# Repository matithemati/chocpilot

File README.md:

# ChocPilot

ChocPilot to przewodowy macropad z **8 niskoprofilowymi klawiszami Kailh Choc** (matryca 2×4)
i **ekranem OLED 2,42" (SSD1309, 128×64)** na **Arduino Pro Micro** (ATmega32U4), oraz aplikacja
na Windows, w której ustawiasz, co robi każdy klawisz.

Firmware jest „cienki”: skanuje klawisze, rysuje ekran i przechowuje kilka ustawień. Całą logikę
(gesty, akcje, profile) wykonuje aplikacja na PC. Komunikują się przez USB CDC protokołem
JSON Lines ([docs/PROTOCOL.md](docs/PROTOCOL.md)). Gdy aplikacja nie działa, urządzenie samo
wysyła zapisane skróty przez USB HID (tryb awaryjny).

Projekt powstał z kodu macropada Tap32 (3×3 MX + enkoder) – ChocPilot nie ma pokrętła.

```
firmware/   PlatformIO: środowiska promicro (5 V), promicro_3v3, native (testy)
app/        aplikacja Python 3.12+ (PySide6): rdzeń, GUI, symulator, testy
docs/       PROTOCOL.md, WIRING.md, schematic.png (schemat płytki)
```

## Funkcje

- **Gesty**: naciśnięcie, przytrzymanie (próg 500 ms), podwójne naciśnięcie (okno 300 ms).
- **Akcje**: uruchom program (albo przełącz na jego okno; przy kilku oknach kolejne naciśnięcia
  przechodzą między nimi), otwórz plik/folder, adres WWW,
  skrót klawiszowy (także Win, F13–F24), wpisz tekst (Unicode), multimedia, głośność
  systemu i pojedynczego programu, przewijanie, polecenie cmd/PowerShell, makro, zmiana
  profilu, warstwa (profil na czas trzymania klawisza), blokada komputera, wyłączenie ekranu.
- **Profile** z automatycznym przełączaniem według aktywnego okna (np. `obs64.exe` → „Stream”),
  import/eksport do JSON.
- **Ekran 128×64**: siatka etykiet 2×4 (jak klawisze) albo duża nazwa profilu, pasek głośności,
  etykieta po akcji, wygaszacz, znacznik online/offline, tryb testu sprzętu.
- **Tryb awaryjny HID**: po 3 s bez sygnału z aplikacji klawisze wysyłają skróty wyliczone
  z profilu (akcje „skrót” i „multimedia”); domyślnie dolny rząd: ciszej, głośniej,
  odtwarzaj/pauza, wycisz.

## Części

- 1× Arduino / SparkFun **Pro Micro** (ATmega32U4), 5 V/16 MHz albo 3,3 V/8 MHz
- 8× przełącznik **Kailh Choc** (low profile) + nasadki Choc, 8× dioda 1N4148
- 1× OLED **2,42" SSD1309 128×64 I²C** – moduł ShengYang, wersja **4-pinowa I²C**
  (70,10 × 48,10 mm, używana w projekcie); wersja 7-pinowa (72 × 43 mm) też pasuje do obudowy
  (`oled_variant`), ale wymaga przełożenia rezystorów z SPI na I²C.
  Szczegóły i karta sprzedawcy: [docs/WIRING.md](docs/WIRING.md#oled-242-ssd1309-12864-ic-złącze-j1)
- płytka ChocPilot (schemat: [docs/schematic.png](docs/schematic.png))

## Montaż

Pełny opis i tabela pinów: **[docs/WIRING.md](docs/WIRING.md)**. Najważniejsze:

1. Matryca **COL2ROW** 2×4: przy każdym przełączniku dioda 1N4148, **pasek (katoda) w stronę
   wiersza**. S1–S4 = klawisze K1–K4 (Row 0), S5–S8 = K5–K8 (Row 1).
2. OLED na złączu J1: GND, **+5 V**, SDA (pin 2 Pro Micro), SCL (pin 3). Sprawdź kolejność
   wyprowadzeń modułu – jeśli SDA i SCL są zamienione, firmware sam to wykryje (programowe I²C).
3. Uruchom tryb testu sprzętu (przytrzymaj **K1 + K4** zaraz po podłączeniu, przez 3 s) i sprawdź
   każdy klawisz.

## Firmware

Wymagania: [PlatformIO](https://platformio.org/) (VS Code + rozszerzenie albo `pip install platformio`).

```bash
cd firmware
pio run -e promicro
```

(`promicro` – Pro Micro 5 V/16 MHz, `promicro_3v3` – wersja 3,3 V/8 MHz.)

Platforma `atmelavr`, płytka `sparkfun_promicro16` (albo `sparkfun_promicro8`), rdzeń Arduino AVR:
USB CDC + HID (PluggableUSB, klawiatura i consumer control). Nazwa USB „ChocPilot”, VID/PID
z definicji płytki SparkFun: **1B4F:9206** (5 V) / **1B4F:9204** (3,3 V). Aplikacja szuka nazwy
„ChocPilot”, a zapasowo tych par oraz klonów z bootloaderem Leonardo/Micro (2341:8036 / 8037) –
nigdy PID-ów bootloadera Caterina (bajty `hello` byłyby dla niego komendami).

ATmega32U4 ma **2,5 KB RAM i 28 KB flash** (z bootloaderem Caterina). Zużycie (sprawdzone
2026-10, `pio run -e promicro`): **flash 25 974 B / 28 672 B (90,6 %)**, **RAM statycznie
1 958 B / 2 560 B (76,5 %)** – reszta to stos (bufor pasa ekranu, parser). Dlatego:

- **Ekran**: zamiast grafiki U8g2 z czcionkami – mini-renderer (`firmware/src/mini_gfx.cpp`)
  na sterowniku U8x8 (SSD1309 `noname2`): jeden krój **5×7 ASCII** w skali 1×–3×, pogrubiony
  i wąski (6 znaków w komórce siatki). **Polskie litery tracą ogonki** (ą → a, Ł → L).
  Podgląd w aplikacji rysuje dokładnie te same piksele.
- **I²C**: sprzętowy TWI 400 kHz (własna obsługa rejestrów, bez biblioteki Wire); gdy ekran
  odpowiada dopiero po zamianie SDA/SCL – programowe I²C na zamienionych pinach.
- **Protokół**: kodek bez bibliotek JSON (czyta linię w miejscu, bez alokacji). Maksymalna linia
  do urządzenia to **272 B** (`max_line` w `hello`); aplikacja sama dzieli dłuższe `set_fallback`.
- **Bufory**: tytuł do 21 znaków ASCII (22 B), etykieta do 10 znaków (12 B) – wielobajtowe UTF-8
  skraca się wcześniej.
- **Ustawienia** w EEPROM jako blok binarny z CRC. Zapis nie jest atomowy: przerwany odłączeniem
  zasilania kończy się wartościami domyślnymi.
- **Brak diody statusu** (RX/TX LED steruje rdzeń USB; stan widać na ekranie).

### Wgrywanie

Skrypt `firmware\flash.ps1` znajduje PlatformIO (PATH, `%USERPROFILE%\.platformio`, a w razie
potrzeby instaluje go przez pip), sprawdza, czy aplikacja nie trzyma portu, kompiluje i wgrywa:

```powershell
cd firmware
.\flash.ps1
```

Opcje: `-Board 3v3` (Pro Micro 3,3 V/8 MHz), `-Port COM7` (konkretny port), `-BuildOnly`
(tylko kompilacja, wynik w `.pio\build\promicro\firmware.hex`), `-CloseApp` (zamyka działającą
aplikację ChocPilot). Bez skryptu: `pio run -e promicro -t upload`.

Najpierw zamknij aplikację ChocPilot (trzyma port COM). PlatformIO otwiera port z prędkością
1200 bps („1200 bps touch”), płytka restartuje się do bootloadera **Caterina** (osobny port COM
na ok. 8 s, potem wraca do programu) i avrdude wgrywa firmware. Menu aplikacji
**Urządzenie → Tryb wgrywania firmware** też przełącza do Caterina (firmware wpisuje „magiczny
klucz” i restartuje się watchdogiem) – przydatne przy wgrywaniu ręcznym avrdude w ciągu tych 8 s.
Gdy firmware nie działa: zewrzyj dwa razy szybko **RST** z **GND** i od razu wgrywaj.

### Testy firmware (na PC)

Parser protokołu, debounce, kody HID i zapis konfiguracji mają testy jednostkowe w środowisku
`native`. Potrzebny jest kompilator gcc/g++ w PATH (Windows: MSYS2/MinGW-w64; najprościej
`pio pkg install -g -t platformio/toolchain-gccmingw32` i dodanie
`%USERPROFILE%\.platformio\packages\toolchain-gccmingw32\bin` do PATH).

```bash
pio test -e native
```

## Aplikacja

Wymagania: Windows 10/11, Python **3.12+** (sprawdzone na 3.14).

```bash
cd app
python -m venv .venv
.venv\Scripts\python -m pip install -e ".[dev]"
.venv\Scripts\python -m chocpilot
```

Opcje:

| Opcja | Działanie |
|---|---|
| `--simulate` | zamiast urządzenia uruchamia **symulator** (okno z 8 klawiszami 2×4 i podglądem OLED 128×64) |
| `--minimized` | start w zasobniku |
| `--config PLIK` | inny plik konfiguracji |
| `--verbose` | dziennik na konsoli |

Konfiguracja: `%APPDATA%\ChocPilot\config.json` (zapis atomowy, poprzednia wersja
w `config.json.bak`, dziennik w `chocpilot.log`). Uszkodzony plik jest odkładany jako
`config.broken.json`, a aplikacja wczytuje kopię zapasową.

Obsługa:

- Lista profili po lewej (dwuklik = aktywuj). Kliknij klawisz na podglądzie, aby edytować;
  przyciski **Testuj** wykonują akcję od razu. Fizyczne naciśnięcia podświetlają klawisze.
- **Plik → Ustawienia**: port (auto/ręczny), jasność, wygaszacz, tryb ekranu, obrót, progi gestów,
  debounce, skróty trybu awaryjnego, autostart z Windows, start zminimalizowany, motyw.
- Zamknięcie okna chowa aplikację do zasobnika (kolor ikony = stan połączenia). Z zasobnika:
  zmiana profilu, **Wstrzymaj akcje**, wyjście. Uruchamia się tylko jedna instancja.

### Testy i jakość

```bash
cd app
.venv\Scripts\python -m pytest
.venv\Scripts\python -m ruff check chocpilot tests
.venv\Scripts\python -m ruff format --check chocpilot tests
```

Testy nie wymagają urządzenia (atrapy portu szeregowego, platformy i symulator). Testy GUI
działają w trybie `offscreen` (pytest-qt).

### Budowanie ChocPilot.exe

```powershell
cd app
.\build_exe.ps1
```

Skrypt instaluje zależności, generuje ikonę (`scripts/make_icon.py`) i uruchamia PyInstaller
(`chocpilot.spec`, jeden plik, bez konsoli). Wynik: `app\dist\ChocPilot.exe`.

### Architektura aplikacji

```
chocpilot/core/protocol.py    kodowanie/dekodowanie JSON Lines, walidacja, transliteracja (OLED = ASCII)
chocpilot/core/transport.py   interfejs + port szeregowy (wątek, wykrywanie, ponowne łączenie)
chocpilot/core/simulator.py   symulator urządzenia (ta sama logika co firmware) + transport w procesie
chocpilot/core/gestures.py    tap / hold / double_tap (czysta logika, czas z zewnątrz)
chocpilot/core/actions/       rejestr typów akcji, wbudowane akcje, wykonawca (pula wątków)
chocpilot/core/config.py      modele pydantic, migracje schema_version, zapis atomowy, import/eksport
chocpilot/core/profiles.py    aktywny profil, warstwy, automatyczne przełączanie
chocpilot/core/engine.py      kontroler: zdarzenia → gesty → akcje; profil → display + set_fallback
chocpilot/platform/           kod zależny od systemu (windows.py; base.py = interfejs dla Linux/macOS)
chocpilot/gui/                PySide6: okno główne, edytory, ustawienia, zasobnik, symulator
chocpilot/gui/oled.py         podgląd OLED 128×64 – ten sam krój i układ co firmware
```

Nowy typ akcji: klasa dziedzicząca po `ActionBase` z polem `type: Literal["nazwa"]`, metodą
`run(ctx)` i dekoratorem `@register_action("nazwa", "Etykieta")`. Formularz w GUI tworzy się
automatycznie z pól modelu.

## Obudowa (OpenSCAD)

`case/chocpilot_case.scad` – obudowa **93,5 × 101 × 20 mm** z płaską górą, symetryczna w obu osiach względem klawiszy i ekranu (lewa i dolna ścianka są grubsze o tyle, o ile PCB wystaje w prawo pod Pro Micro i ma większy margines nad górnym rzędem), dopasowana do
kompaktowej płytki z KiCad (`esp_macropad/pcb/tap32/tap32.kicad_pcb`, podgląd:
[docs/img/pcb_compact.png](docs/img/pcb_compact.png)): obrys 79,5 × 88,75 mm, rzędy klawiszy
67 mm od siebie, ekran 2,42" poziomo dokładnie pośrodku (ten sam odstęp od obu rzędów).
Moduł OLED wisi 2 mm nad płytką, przykręcony od spodu do płyty obudowy (4× M2,5×4); szkło leży
w otworze 0,4 mm poniżej powierzchni – nic nie wystaje. Płytka leży na 5 słupkach dna (M3),
Pro Micro od spodu (wystaje 1,9 mm poza PCB – kieszeń w prawej ściance), USB wychodzi prawą
ścianką. Skorupa drukuje się górą w dół bez podpór.

Pod modułem musi być płasko (2 mm wolnego miejsca):

- wkręty płytki **M3 z niskim łbem** (ISO 7380 / „button head”, łeb 1,65 mm) – wszystkie
  otwory H1–H5 leżą pod modułem,
- piny Pro Micro od góry płytki **przycięte równo z lutem**,
- moduł połączony **przewodami** (cienkie, np. AWG 28–30) z polami J1 – bez złącza XH;
  złącze na dolnej krawędzi modułu 4-pinowego (od spodu) zdejmij, jeśli jest wyższe niż 2 mm.

```bash
openscad -D part=\"shell\" -o chocpilot_shell.stl case/chocpilot_case.scad
```

```bash
openscad -D part=\"bottom\" -o chocpilot_bottom.stl case/chocpilot_case.scad
```

Części: `shell`, `bottom`; podgląd: `assembly`, `exploded`.

**Moduł OLED:** ShengYang 2,42", wersja wybierana parametrem `oled_variant` – `i2c_4pin`
(domyślnie, 70,10 × 48,10 mm) albo `spi_7pin` (72 × 43 mm). Wymiary płytek są z karty
sprzedawcy, ale rozstaw otworów (ok. 3 mm od krawędzi) i położenie szkła są oszacowane –
**zmierz moduł przed drukiem**. Plik sprawdza asercjami przy renderowaniu, że szkło nie
wystaje, moduł nie nachodzi na przełączniki i że wokół wkrętów modułu zostaje materiał płyty
(1,6 mm do otworów na klawisze, 1,2 mm do otworu na szkło). Zakładany jest też
montaż Pro Micro od spodu płytki (elementy w dół) – przy montażu od góry trzeba zmienić
`standoff_h`, wycięcie USB i miejsce pod modułem.

## Rozwiązywanie problemów

| Objaw | Co sprawdzić |
|---|---|
| Aplikacja „szuka ChocPilot…” | Kabel z transmisją danych (nie tylko ładowanie). Zamknij monitor portu PlatformIO/Arduino IDE (port może być zajęty). W Ustawieniach wybierz port ręcznie. Dziennik pokazuje próby. |
| Wgrywanie kończy się błędem / brak portu | Dwa razy szybko zewrzyj RST z GND i od razu uruchom `pio run -e promicro -t upload`. Klon z bootloaderem Leonardo ma VID 2341 – aplikacja też go znajdzie (PID 8036/8037). |
| Pusty ekran | Spójrz na pasek stanu aplikacji: **OLED: 0x3C/0x3D** = ekran odpowiada (adres wybierany automatycznie), **OLED: brak** = nic nie odpowiada na I²C – sprawdź zasilanie +5 V, GND, czy moduł 2,42" jest ustawiony na I²C (nie SPI) i lutowanie. Lista znalezionych urządzeń jest w zakładce Dziennik. |
| Ekran odpowiada, ale obraz jest przesunięty / śmieci | Niektóre moduły SSD1309 potrzebują innego wariantu sterownika: w `firmware/src/mini_gfx.cpp` zamień `u8x8_d_ssd1309_128x64_noname2` na `..._noname0`. |
| Polskie litery bez ogonków | To nie błąd: firmware ma tylko krój ASCII (brak miejsca na czcionki). |
| Kilka klawiszy reaguje naraz | Odwrócona dioda albo brak diody; sprawdź w trybie testu sprzętu. |
| Klawisz „drga” | Zwiększ debounce (Ustawienia → Urządzenie). |
| Przełączanie na okno programu nie działa | Windows czasem blokuje przejęcie fokusu; program i tak jest uruchamiany, gdy nie ma okna. |
| Głośność programu „nie gra” | Program musi mieć aktywną sesję audio (widoczną w mikserze głośności). |
| SmartScreen / antywirus ostrzega o ChocPilot.exe | Plik nie jest podpisany; pynput (symulacja klawiatury) bywa oznaczany heurystycznie. Można uruchamiać z Pythona. |
| Akcje wykonują się podwójnie | Nie powinno: gdy aplikacja jest połączona, HID urządzenia jest wyłączony. Sprawdź, czy nie działają dwie kopie aplikacji (np. exe i python). |

## Licencja

MIT.

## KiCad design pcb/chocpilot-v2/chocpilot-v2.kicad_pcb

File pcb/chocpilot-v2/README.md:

# ChocPilot v2 – płytka (KiCad 10)

Druga wersja sprzętu ChocPilot: 8 klawiszy Kailh Choc V2 w gniazdach hotswap (2 rzędy po 4),
poziomy ekran OLED 2,42" I²C pomiędzy nimi, 2 enkodery EC11 po lewej, suwak 45 mm po prawej,
12 diod WS2812B na spodzie (podświetlenie blatu) i własny mikrokontroler STM32F072 z USB-C.
Płytka 110 × 93 mm, 2 warstwy, wszystko poza elementami istniejącymi tylko w THT – SMD
w obudowach do ręcznego lutowania (0805, SOT-23, LQFP-48).

| Plik | Zawartość |
|---|---|
| `chocpilot-v2.kicad_pro/.kicad_sch/.kicad_pcb` | projekt KiCad 10 (schemat A3, płytka z trasami i wylewkami GND) |
| `chocpilot.pretty/` | footprint własny: Kailh Choc V1/V2 z gniazdem hotswap |
| [bom/BOM.md](bom/BOM.md), [bom/chocpilot-v2-bom.csv](bom/chocpilot-v2-bom.csv) | lista części z numerami TME / Amazon |
| [docs/PINOUT.md](docs/PINOUT.md) | mapa pinów MCU, złącza, kolejność LED |
| [docs/ASSEMBLY.md](docs/ASSEMBLY.md) | kolejność lutowania i uruchomienie |
| [docs/DESIGN_NOTES.md](docs/DESIGN_NOTES.md) | decyzje projektowe, zasilanie, co trzeba zmienić w firmware/aplikacji/obudowie |
| `img/` | podgląd: `schematic.pdf/.png`, `pcb_top/bottom.png` (warstwy), `render_top/bottom.png` (3D) |
| `fab/chocpilot-v2-gerbers.zip` | Gerbery + wiercenia do zamówienia płytek |
| `tools/` | generatory – patrz niżej |

## Dlaczego STM32F072CBT6, a nie RP2040

- **Obudowa.** RP2040 istnieje tylko jako QFN-56 0,4 mm z padem termicznym pod spodem – bez
  gorącego powietrza / pieca praktycznie nie do przylutowania kolbą. STM32F072CBT6 to
  **LQFP-48 0,5 mm z wyprowadzeniami na zewnątrz**: lutuje się zwykłą kolbą metodą „drag”
  z topnikiem, a mostki widać i łatwo zebrać plecionką.
- **Mniej części.** F072 ma USB FS **bez kwarcu** (HSI48 synchronizowany przez CRS z ramkami
  USB), pamięć programu w środku (128 KB) i **bootloader USB DFU w ROM** (BOOT0 + RESET).
  RP2040 wymaga zewnętrznego flasha QSPI (SOIC-8 lub USON), kwarcu 12 MHz i dodatkowego
  odsprzęgania wewnętrznego regulatora 1,1 V.
- **Wystarczająca wydajność.** Firmware v1 mieści się w ATmega32U4 (32 KB flash / 2,5 KB RAM);
  F072 ma 128 KB / 16 KB, sprzętowe I²C, ADC 12-bit, timery z trybem enkodera (TIM2, TIM3)
  i SPI do sterowania WS2812.
- **Dostępność.** STM32F072CBT6 jest w TME, wspierany przez STM32duino (PlatformIO `ststm32`)
  i QMK.

Kwarc 8 MHz (Y1) jest na płytce jako **opcja** – USB go nie potrzebuje; daje dokładniejszy zegar,
jeśli kiedyś będzie potrzebny (można nie lutować Y1, C13, C14).

## Weryfikacja (KiCad 10.0.7, `kicad-cli`)

- **ERC:** 0 błędów, 0 ostrzeżeń.
- **DRC** (`--severity-all --schematic-parity`, także z `--refill-zones`): 0 naruszeń,
  0 niepołączonych, 0 rozbieżności ze schematem.
- Reguły: odstęp miedź–miedź 0,2 mm, ścieżki 0,25 mm (sygnały) / 0,3 mm (+3V3, GND) /
  0,6 mm (VBUS, +5V), przelotki 0,6/0,3 mm, krawędź 0,3 mm (trasowane z 0,5 mm), otwór–miedź
  0,15 mm (kołki ustalające USB-C mają 0,19 mm do padów GND w bibliotecznym footprincie).
  Mieści się w standardzie tanich fabryk (JLCPCB, PCBWay: 2 warstwy, 1,6 mm, 1 oz).

Do zrobienia przed zamówieniem płytek – patrz [DESIGN_NOTES.md](docs/DESIGN_NOTES.md#do-sprawdzenia-przed-zamowieniem):
wydruk 1:1 i przymiarka gniazda Choc, położenie i raster pinów Twojego modułu OLED.

## Generowanie

Schemat, płytka i BOM powstają ze skryptów w `tools/` (dane: [`tools/design.py`](tools/design.py)).
Ręczne poprawki w KiCad są możliwe, ale kolejne generowanie je nadpisze – zmieniaj `design.py`.

```bash
cd pcb/chocpilot-v2
python3 tools/gen_pro.py        # reguły DRC i klasy sieci
python3 tools/gen_sch.py        # schemat
/Applications/KiCad/KiCad.app/Contents/Frameworks/Python.framework/Versions/Current/bin/python3 tools/gen_pcb.py
python3 tools/gen_bom.py        # BOM.md + CSV
tools/render.sh img             # podgląd PNG
tools/export_fab.sh             # Gerbery
```

`gen_pcb.py` używa Pythona dołączonego do KiCad (moduł `pcbnew`), eksportuje netlistę ze
schematu przez `kicad-cli` i trasuje płytkę własnym routerem [`tools/router.py`](tools/router.py)
(A* na siatce 0,25 mm, 2 warstwy; ok. 1 min). `--reuse` używa zapisanych tras z
`tools/build/`. Na macOS `kicad-cli` uruchamiany z piaskownicy potrafi zawisnąć przy starcie –
wtedy trzeba go uruchomić poza nią.

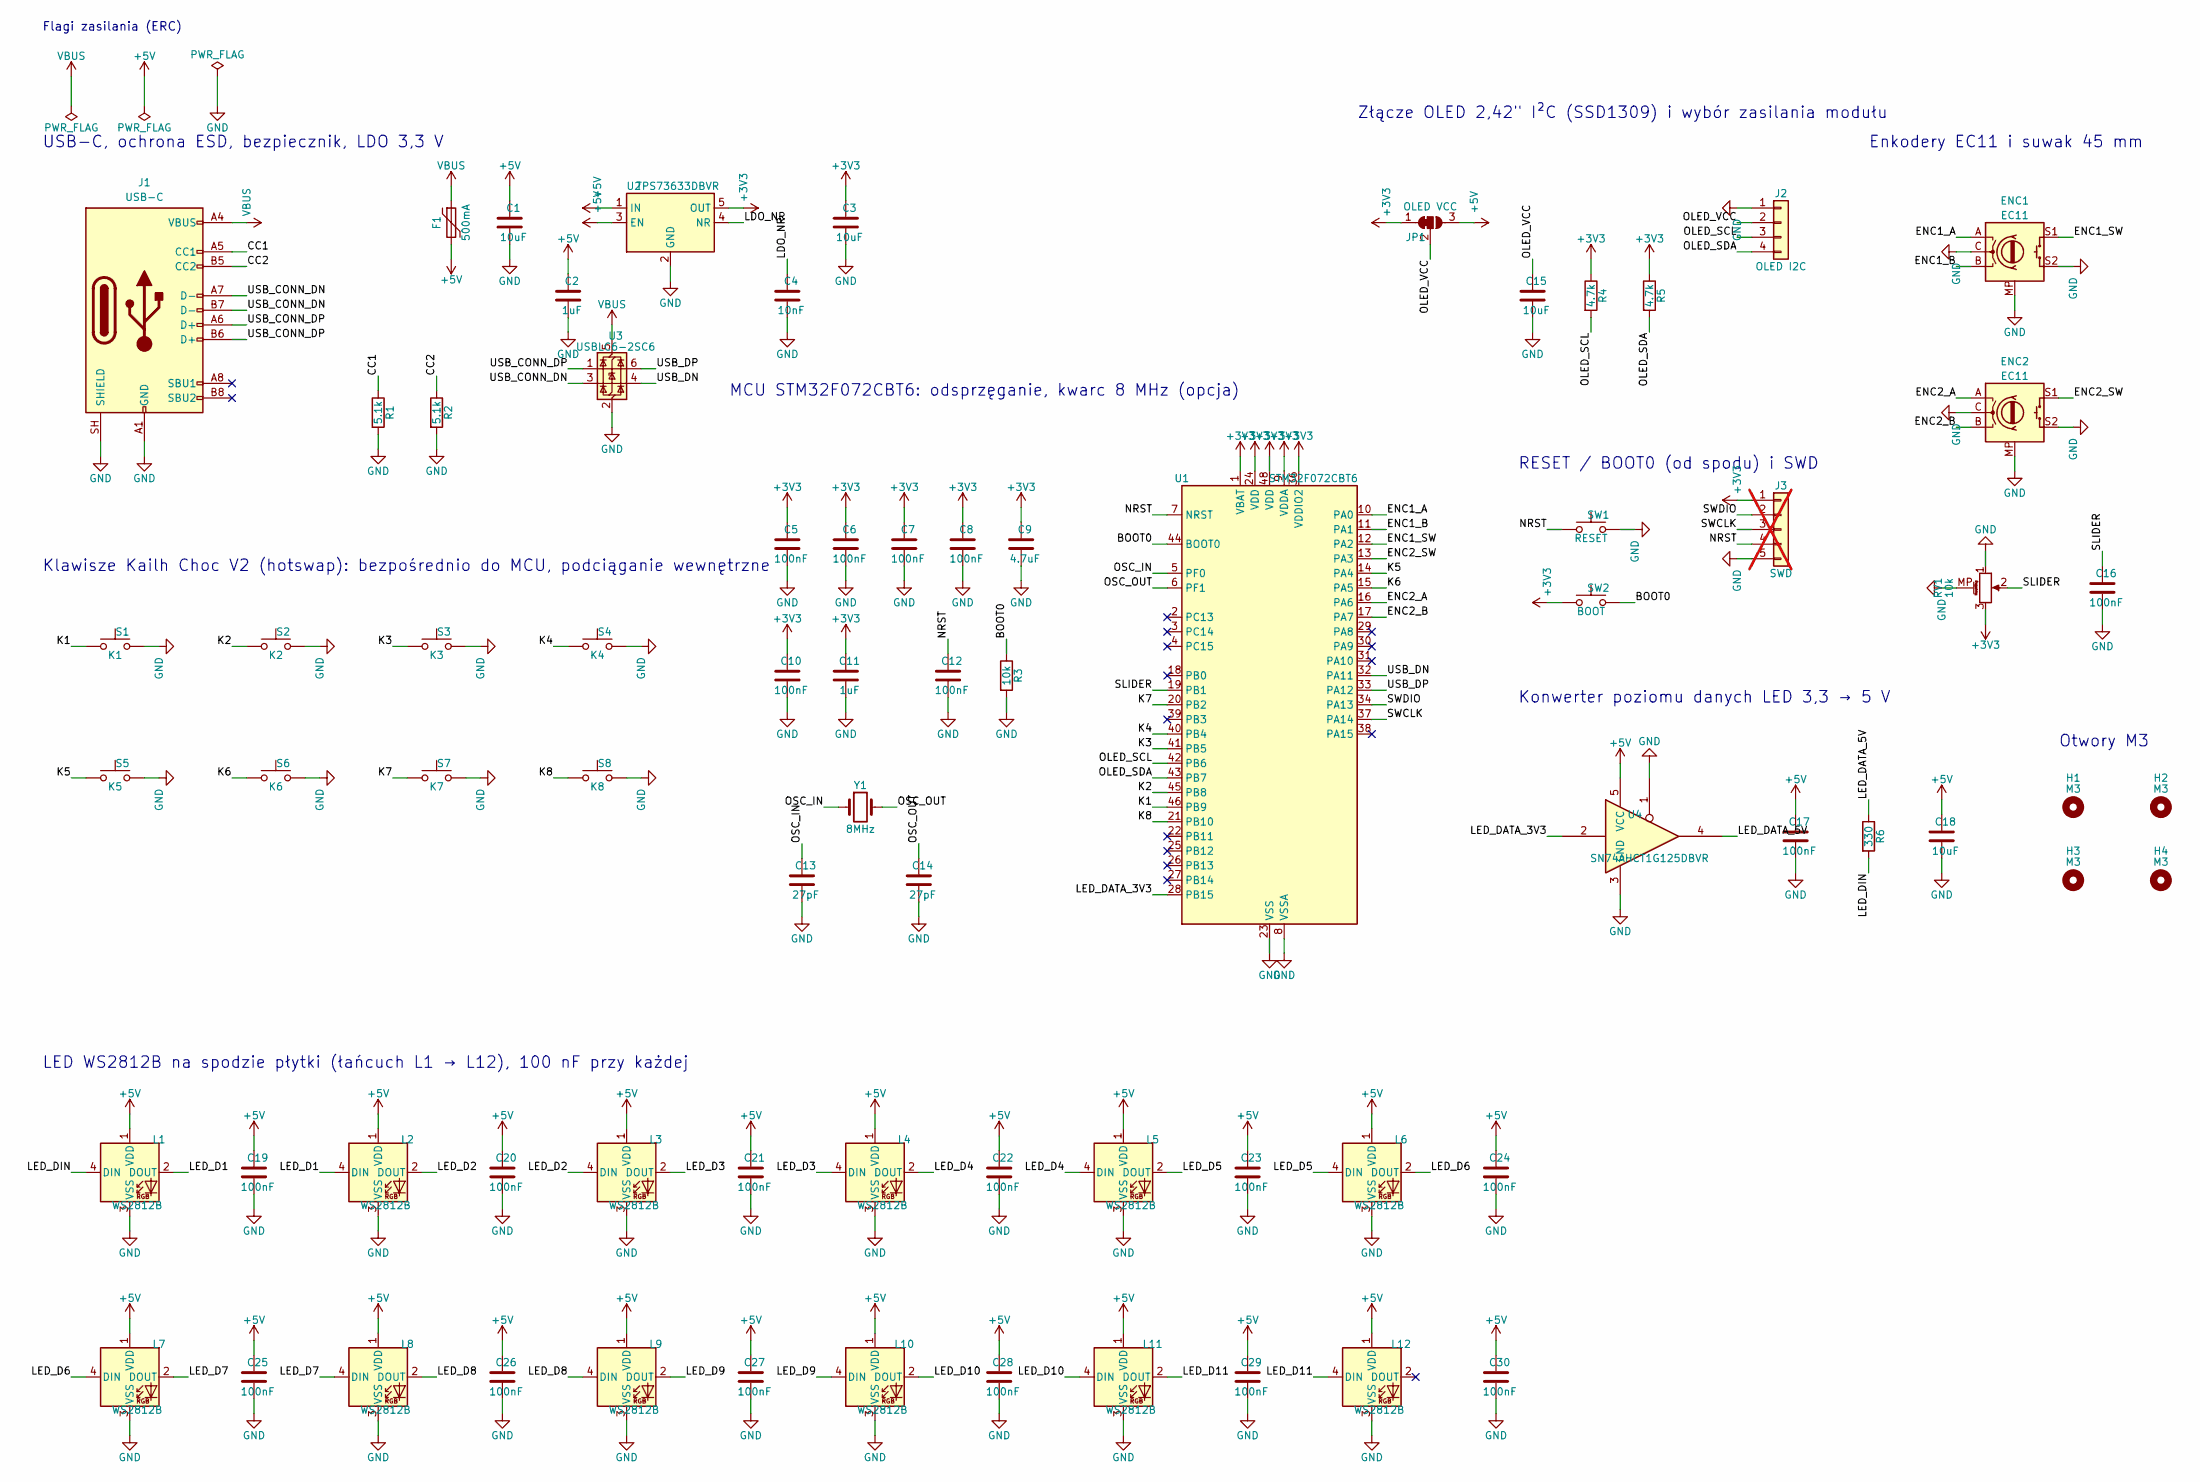
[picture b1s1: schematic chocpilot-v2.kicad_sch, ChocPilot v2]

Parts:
C1, C3, C15, C18: 10uF; C_0805_2012Metric_Pad1.18x1.45mm_HandSolder; MPN CL21A106KAYNNNE
C2, C11: 1uF; C_0805_2012Metric_Pad1.18x1.45mm_HandSolder; MPN CL21B105KBFNNNE
C4: 10nF; C_0805_2012Metric_Pad1.18x1.45mm_HandSolder; MPN CL21B103KBANNNC
C5, C6, C7, C8, C10, C12, C16, C17, C19, C20, C21, C22, C23, C24, C25, C26, C27, C28, C29, C30: 100nF; C_0805_2012Metric_Pad1.18x1.45mm_HandSolder; MPN CL21B104KBCNNNC
C9: 4.7uF; C_0805_2012Metric_Pad1.18x1.45mm_HandSolder; MPN CL21A475KAQNNNE
C13, C14: 27pF; C_0805_2012Metric_Pad1.18x1.45mm_HandSolder; MPN CL21C270JBANNNC
ENC1, ENC2: EC11; RotaryEncoder_Alps_EC11E-Switch_Vertical_H20mm; MPN EC11E15244G1
F1: 500mA; Fuse_1206_3216Metric_Pad1.42x1.75mm_HandSolder; MPN MF-NSMF050-2
H1, H2, H3, H4: M3; MountingHole_3.2mm_M3
J1: USB-C; USB_C_Receptacle_GCT_USB4105-xx-A_16P_TopMnt_Horizontal; MPN USB4105-GF-A
J2: OLED I2C; PinSocket_1x04_P2.54mm_Vertical; MPN DS1023-1*4S21
J3: SWD; PinHeader_1x05_P2.54mm_Vertical; MPN DS1021-1*5SF11-B; not fitted
JP1: OLED VCC; SolderJumper-3_P1.3mm_Bridged12_RoundedPad1.0x1.5mm
L1, L2, L3, L4, L5, L6, L7, L8, L9, L10, L11, L12: WS2812B; LED_WS2812B_PLCC4_5.0x5.0mm_P3.2mm; MPN WS2812B-V5
R1, R2: 5.1k; R_0805_2012Metric_Pad1.20x1.40mm_HandSolder; MPN RC0805FR-075K1L
R3: 10k; R_0805_2012Metric_Pad1.20x1.40mm_HandSolder; MPN RC0805FR-0710KL
R4, R5: 4.7k; R_0805_2012Metric_Pad1.20x1.40mm_HandSolder; MPN RC0805FR-074K7L
R6: 330; R_0805_2012Metric_Pad1.20x1.40mm_HandSolder; MPN RC0805FR-07330RL
RV1: 10k; Potentiometer_Bourns_PTA4543_Single_Slide; MPN PTA4543-2015DPA103
S1: K1; SW_Kailh_Choc_V1V2_Hotswap_1u; MPN CPG135001S30 (gniazdo) + CPG1353 (Choc 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
S2: K2; SW_Kailh_Choc_V1V2_Hotswap_1u; MPN CPG135001S30 (gniazdo) + CPG1353 (Choc 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
S3: K3; SW_Kailh_Choc_V1V2_Hotswap_1u; MPN CPG135001S30 (gniazdo) + CPG1353 (Choc 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
S4: K4; SW_Kailh_Choc_V1V2_Hotswap_1u; MPN CPG135001S30 (gniazdo) + CPG1353 (Choc 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
S5: K5; SW_Kailh_Choc_V1V2_Hotswap_1u; MPN CPG135001S30 (gniazdo) + CPG1353 (Choc 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
S6: K6; SW_Kailh_Choc_V1V2_Hotswap_1u; MPN CPG135001S30 (gniazdo) + CPG1353 (Choc 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
S7: K7; SW_Kailh_Choc_V1V2_Hotswap_1u; MPN CPG135001S30 (gniazdo) + CPG1353 (Choc 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
S8: K8; SW_Kailh_Choc_V1V2_Hotswap_1u; MPN CPG135001S30 (gniazdo) + CPG1353 (Choc 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
SW1: RESET; SW_SPST_PTS645Sx43SMTR92; MPN PTS645SM43SMTR92 LFS
SW2: BOOT; SW_SPST_PTS645Sx43SMTR92; MPN PTS645SM43SMTR92 LFS
U1: STM32F072CBT6; LQFP-48_7x7mm_P0.5mm; MPN STM32F072CBT6
U2: TPS73633DBVR; SOT-23-5_HandSoldering; MPN TPS73633DBVR
U3: USBLC6-2SC6; SOT-23-6_Handsoldering; MPN USBLC6-2SC6
U4: SN74AHCT1G125DBVR; SOT-23-5_HandSoldering; MPN SN74AHCT1G125DBVR
Y1: 8MHz; Crystal_SMD_5032-2Pin_5.0x3.2mm_HandSoldering; MPN ABM3-8.000MHZ-D2Y-T

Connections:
+3V3: C3.1, C5.1, C6.1, C7.1, C8.1, C9.1, C10.1, C11.1, J3.1, JP1.1 (A), R4.1, R5.1, RV1.3, SW2.1, U1.1 (VBAT), U1.9 (VDDA), U1.24 (VDD), U1.36 (VDDIO2), U1.48 (VDD), U2.5 (OUT)
+5V: C1.1, C2.1, C17.1, C18.1, C19.1, C20.1, C21.1, C22.1, C23.1, C24.1, C25.1, C26.1, C27.1, C28.1, C29.1, C30.1, F1.2, JP1.3 (B), L1.1 (VDD), L2.1 (VDD), L3.1 (VDD), L4.1 (VDD), L5.1 (VDD), L6.1 (VDD), L7.1 (VDD), L8.1 (VDD), L9.1 (VDD), L10.1 (VDD), L11.1 (VDD), L12.1 (VDD), U2.1 (IN), U2.3 (EN), U4.5 (VCC)
/BOOT0: R3.1, SW2.2, U1.44 (BOOT0)
/CC1: J1.A5 (CC1), R1.1
/CC2: J1.B5 (CC2), R2.1
/ENC1_A: ENC1.A, U1.10 (PA0)
/ENC1_B: ENC1.B, U1.11 (PA1)
/ENC1_SW: ENC1.S1, U1.12 (PA2)
/ENC2_A: ENC2.A, U1.16 (PA6)
/ENC2_B: ENC2.B, U1.17 (PA7)
/ENC2_SW: ENC2.S1, U1.13 (PA3)
/K1: S1.1, U1.46 (PB9)
/K2: S2.1, U1.45 (PB8)
/K3: S3.1, U1.41 (PB5)
/K4: S4.1, U1.40 (PB4)
/K5: S5.1, U1.14 (PA4)
/K6: S6.1, U1.15 (PA5)
/K7: S7.1, U1.20 (PB2)
/K8: S8.1, U1.21 (PB10)
/LDO_NR: C4.1, U2.4 (NR)
/LED_D1: L1.2 (DOUT), L2.4 (DIN)
/LED_D2: L2.2 (DOUT), L3.4 (DIN)
/LED_D3: L3.2 (DOUT), L4.4 (DIN)
/LED_D4: L4.2 (DOUT), L5.4 (DIN)
/LED_D5: L5.2 (DOUT), L6.4 (DIN)
/LED_D6: L6.2 (DOUT), L7.4 (DIN)
/LED_D7: L7.2 (DOUT), L8.4 (DIN)
/LED_D8: L8.2 (DOUT), L9.4 (DIN)
/LED_D9: L9.2 (DOUT), L10.4 (DIN)
/LED_D10: L10.2 (DOUT), L11.4 (DIN)
/LED_D11: L11.2 (DOUT), L12.4 (DIN)
/LED_DATA_3V3: U1.28 (PB15), U4.2
/LED_DATA_5V: R6.1, U4.4
/LED_DIN: L1.4 (DIN), R6.2
/NRST: C12.1, J3.4, SW1.1, U1.7 (NRST)
/OLED_SCL: J2.3, R4.2, U1.42 (PB6)
/OLED_SDA: J2.4, R5.2, U1.43 (PB7)
/OLED_VCC: C15.1, J2.2, JP1.2 (C)
/OSC_IN: C13.1, U1.5 (PF0), Y1.1
/OSC_OUT: C14.1, U1.6 (PF1), Y1.2
/SLIDER: C16.1, RV1.2, U1.19 (PB1)
/SWCLK: J3.3, U1.37 (PA14)
/SWDIO: J3.2, U1.34 (PA13)
/USB_CONN_DN: J1.A7 (D-), J1.B7 (D-), U3.3 (I/O2)
/USB_CONN_DP: J1.A6 (D+), J1.B6 (D+), U3.1 (I/O1)
/USB_DN: U1.32 (PA11), U3.4 (I/O2)
/USB_DP: U1.33 (PA12), U3.6 (I/O1)
GND: C1.2, C2.2, C3.2, C4.2, C5.2, C6.2, C7.2, C8.2, C9.2, C10.2, C11.2, C12.2, C13.2, C14.2, C15.2, C16.2, C17.2, C18.2, C19.2, C20.2, C21.2, C22.2, C23.2, C24.2, C25.2, C26.2, C27.2, C28.2, C29.2, C30.2, ENC1.C, ENC1.MP, ENC1.S2, ENC2.C, ENC2.MP, ENC2.S2, J1.A1 (GND), J1.A12 (GND), J1.B1 (GND), J1.B12 (GND), J1.SH (SHIELD), J2.1, J3.5, L1.3 (VSS), L2.3 (VSS), L3.3 (VSS), L4.3 (VSS), L5.3 (VSS), L6.3 (VSS), L7.3 (VSS), L8.3 (VSS), L9.3 (VSS), L10.3 (VSS), L11.3 (VSS), L12.3 (VSS), R1.2, R2.2, R3.2, RV1.1, RV1.MP (MountPin), S1.2, S2.2, S3.2, S4.2, S5.2, S6.2, S7.2, S8.2, SW1.2, U1.8 (VSSA), U1.23 (VSS), U1.35 (VSS), U1.47 (VSS), U2.2 (GND), U3.2 (GND), U4.1, U4.3 (GND)
VBUS: F1.1, J1.A4 (VBUS), J1.A9 (VBUS), J1.B4 (VBUS), J1.B9 (VBUS), U3.5 (VBUS)

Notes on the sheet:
USB-C, ochrona ESD, bezpiecznik, LDO 3,3 V
MCU STM32F072CBT6: odsprzęganie, kwarc 8 MHz (opcja)
Złącze OLED 2,42" I²C (SSD1309) i wybór zasilania modułu
Enkodery EC11 i suwak 45 mm
Klawisze Kailh Choc V2 (hotswap): bezpośrednio do MCU, podciąganie wewnętrzne
RESET / BOOT0 (od spodu) i SWD
Konwerter poziomu danych LED 3,3 → 5 V
LED WS2812B na spodzie płytki (łańcuch L1 → L12), 100 nF przy każdej
Otwory M3
Flagi zasilania (ERC)

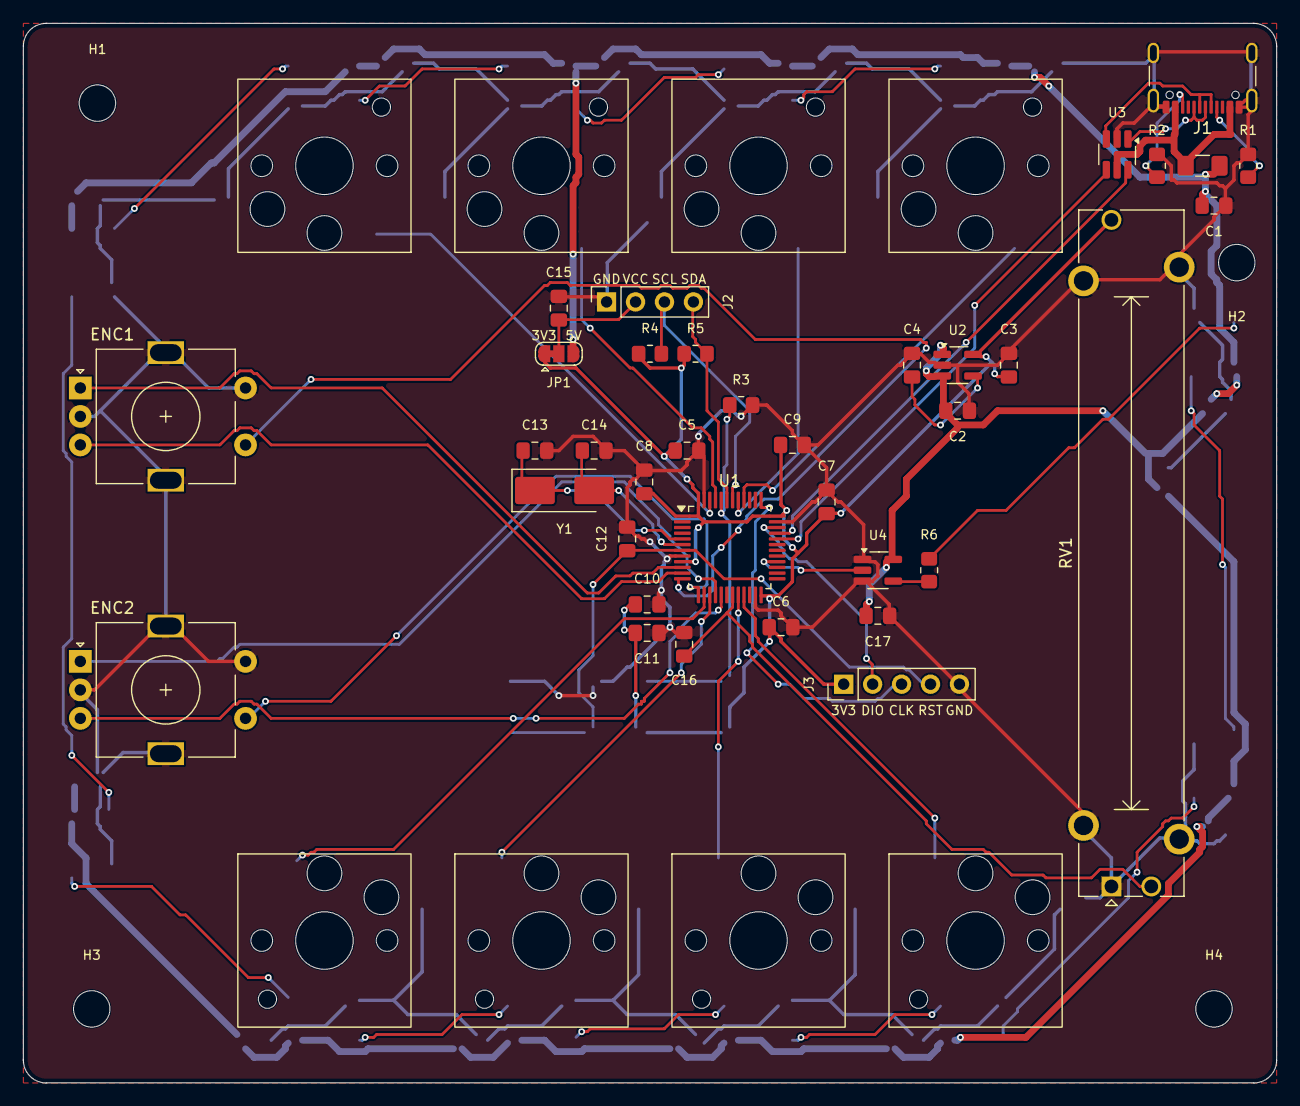
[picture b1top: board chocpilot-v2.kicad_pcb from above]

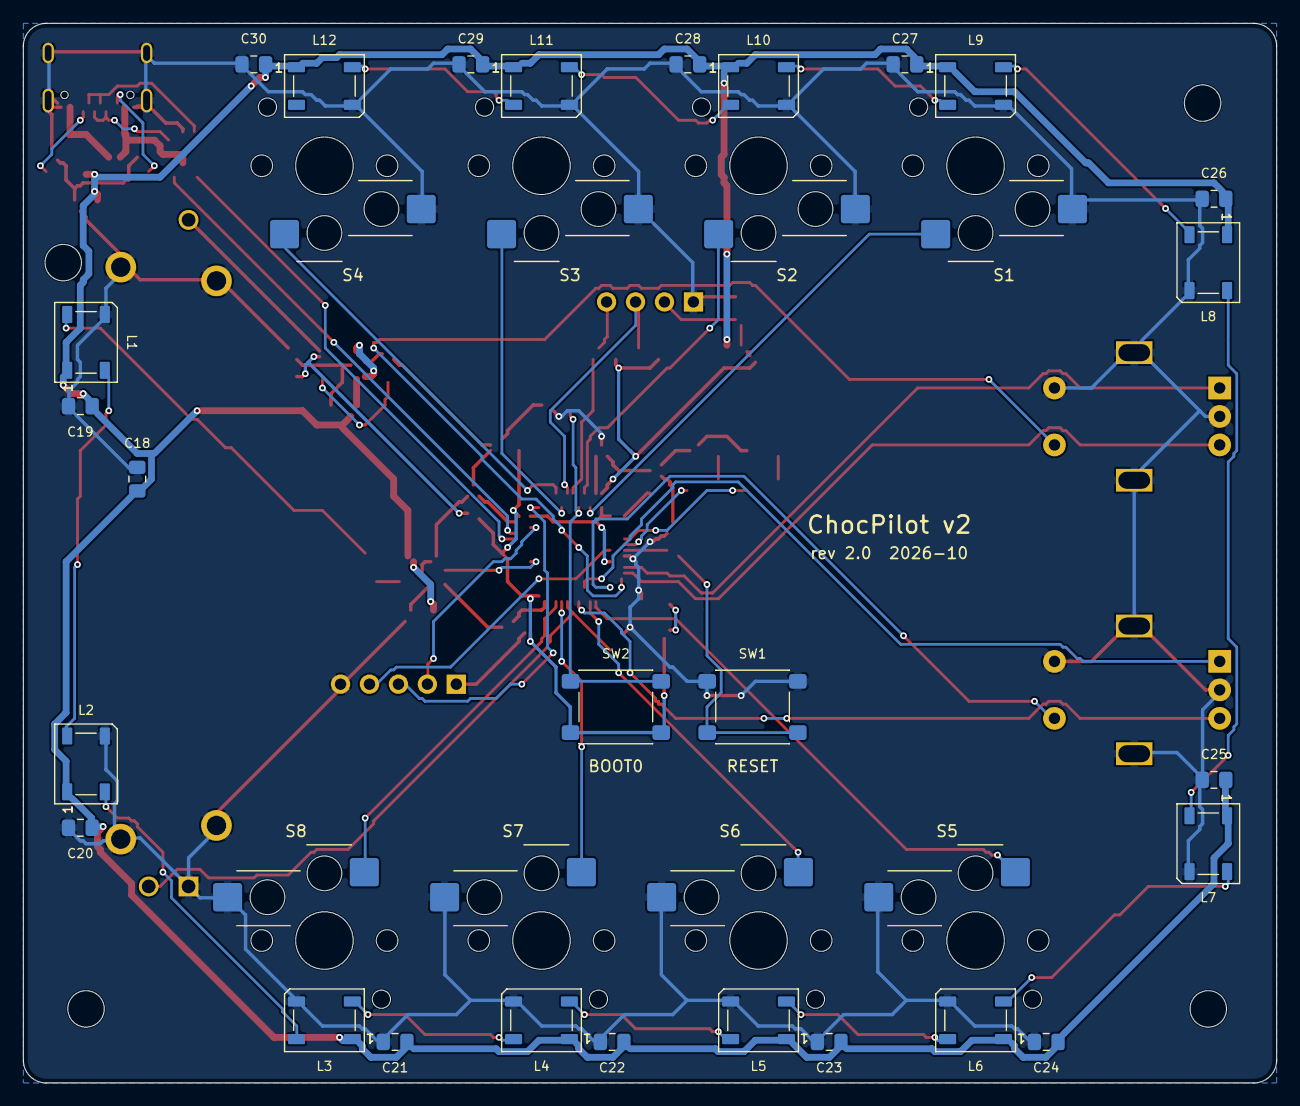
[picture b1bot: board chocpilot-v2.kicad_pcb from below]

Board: 2 copper layers, 110.0 x 93.0 mm, 75 parts (27 on the bottom side), 49 nets.

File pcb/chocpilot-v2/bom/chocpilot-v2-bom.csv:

Poz.,Oznaczenia,Ilość,Opis,Obudowa,Footprint KiCad,Producent,Nr producenta,TME,Amazon (alternatywa),Montaż,Uwagi
1,J1,1,"USB-C 2.0, wlutowane 16 padów SMD (raster 0,5) + 4 kołki THT",SMD 16P + THT,Connector_USB:USB_C_Receptacle_GCT_USB4105-xx-A_16P_TopMnt_Horizontal,GCT,USB4105-GF-A,USB4105-GF-A,,SMD,
2,F1,1,"Bezpiecznik polimerowy PTC 0,5 A (zadziałanie 1 A)",1206,Fuse:Fuse_1206_3216Metric_Pad1.42x1.75mm_HandSolder,Bourns,MF-NSMF050-2,MF-NSMF050-2,,SMD,
3,"R1, R2",2,Rezystor 5.1kΩ 1% 0805,0805,Resistor_SMD:R_0805_2012Metric_Pad1.20x1.40mm_HandSolder,Yageo,RC0805FR-075K1L,RC0805FR-075K1,,SMD,
4,U3,1,Ochrona ESD linii D+/D−,SOT-23-6,Package_TO_SOT_SMD:SOT-23-6_Handsoldering,STMicroelectronics,USBLC6-2SC6,USBLC6-2SC6,,SMD,
5,U2,1,"LDO 3,3 V / 400 mA",SOT-23-5,Package_TO_SOT_SMD:SOT-23-5_HandSoldering,Texas Instruments,TPS73633DBVR,TPS73633DBVR,,SMD,
6,"C1, C3, C15, C18",4,Kondensator 10µF X5R 0805,0805,Capacitor_SMD:C_0805_2012Metric_Pad1.18x1.45mm_HandSolder,Samsung,CL21A106KAYNNNE,CL21A106KAYNNNE,,SMD,
7,"C2, C11",2,Kondensator 1µF X7R 0805,0805,Capacitor_SMD:C_0805_2012Metric_Pad1.18x1.45mm_HandSolder,Samsung,CL21B105KBFNNNE,CL21B105KBFNNNE,,SMD,nr TME do potwierdzenia
8,C4,1,Kondensator 10nF X7R 0805,0805,Capacitor_SMD:C_0805_2012Metric_Pad1.18x1.45mm_HandSolder,Samsung,CL21B103KBANNNC,CL21B103KBANNNC,,SMD,nr TME do potwierdzenia
9,U1,1,"MCU Cortex-M0 48 MHz, USB FS bez kwarcu, bootloader DFU w ROM","LQFP-48 0,5 mm",Package_QFP:LQFP-48_7x7mm_P0.5mm,STMicroelectronics,STM32F072CBT6,STM32F072CBT6,,SMD,
10,"C5–C8, C10, C12, C16, C17, C19–C30",20,Kondensator 100nF X7R 0805,0805,Capacitor_SMD:C_0805_2012Metric_Pad1.18x1.45mm_HandSolder,Samsung,CL21B104KBCNNNC,CL21B104KBCNNNC,,SMD,
11,C9,1,Kondensator 4.7µF X5R 0805,0805,Capacitor_SMD:C_0805_2012Metric_Pad1.18x1.45mm_HandSolder,Samsung,CL21A475KAQNNNE,CL21A475KAQNNNE,,SMD,
12,Y1,1,"Kwarc 8 MHz, CL 18 pF (opcjonalny – USB działa z HSI48+CRS)",5032 2-pad,Crystal:Crystal_SMD_5032-2Pin_5.0x3.2mm_HandSoldering,Abracon,ABM3-8.000MHZ-D2Y-T,ABM3-8.000MHZ-D2Y,,SMD,opcjonalny – USB działa bez kwarcu
13,"C13, C14",2,Kondensator 27pF C0G 0805,0805,Capacitor_SMD:C_0805_2012Metric_Pad1.18x1.45mm_HandSolder,Samsung,CL21C270JBANNNC,CL21C270JBANNNC,,SMD,nr TME do potwierdzenia
14,R3,1,Rezystor 10kΩ 1% 0805,0805,Resistor_SMD:R_0805_2012Metric_Pad1.20x1.40mm_HandSolder,Yageo,RC0805FR-0710KL,RC0805FR-0710K,,SMD,nr TME do potwierdzenia
15,SW1,1,Reset (od spodu płytki),SMD 6×6 mm,Button_Switch_SMD:SW_SPST_PTS645Sx43SMTR92,C&K,PTS645SM43SMTR92 LFS,PTS645SM43SMTR92,,SMD (spód),
16,SW2,1,BOOT0 – wejście do bootloadera DFU (od spodu płytki),SMD 6×6 mm,Button_Switch_SMD:SW_SPST_PTS645Sx43SMTR92,C&K,PTS645SM43SMTR92 LFS,PTS645SM43SMTR92,,SMD (spód),
17,J3,1,"SWD do debugowania (opcjonalne, pady bez listwy)","THT 2,54 mm",Connector_PinHeader_2.54mm:PinHeader_1x05_P2.54mm_Vertical,Connfly,DS1021-1*5SF11-B,ZL201-05G,,THT,DNP – opcjonalne; nr TME do potwierdzenia
18,J2,1,"Złącze modułu OLED 2,42"": GND, VCC, SCL, SDA (jak nadruk modułu)","THT 2,54 mm gniazdo",Connector_PinSocket_2.54mm:PinSocket_1x04_P2.54mm_Vertical,Connfly,DS1023-1*4S21,ZL262-4SG,,THT,
19,"R4, R5",2,Rezystor 4.7kΩ 1% 0805,0805,Resistor_SMD:R_0805_2012Metric_Pad1.20x1.40mm_HandSolder,Yageo,RC0805FR-074K7L,RC0805FR-074K7,,SMD,nr TME do potwierdzenia
20,"ENC1, ENC2",2,Enkoder EC11 z przyciskiem (15 imp./30 zatrzasków),THT,Rotary_Encoder:RotaryEncoder_Alps_EC11E-Switch_Vertical_H20mm,ALPS,EC11E15244G1,EC11E15244G1,,THT,
21,RV1,1,"Potencjometr suwakowy 45 mm, 10 kΩ (dół = GND, góra = 3,3 V)",THT,Potentiometer_THT:Potentiometer_Bourns_PTA4543_Single_Slide,Bourns,PTA4543-2015DPA103,PTA45432015DPA10-0,Bourns PTA4543-2015DPB103 (liniowy),THT,TME ma tylko charakterystykę log. (A) – firmware linearyzuje; liniowa B103 – Amazon
22,U4,1,"Konwerter poziomu 3,3 V → 5 V dla linii danych LED",SOT-23-5,Package_TO_SOT_SMD:SOT-23-5_HandSoldering,Texas Instruments,SN74AHCT1G125DBVR,SN74AHCT1G125DBVR,,SMD,
23,R6,1,Rezystor 330Ω 1% 0805,0805,Resistor_SMD:R_0805_2012Metric_Pad1.20x1.40mm_HandSolder,Yageo,RC0805FR-07330RL,RC0805FR-07330R,,SMD,nr TME do potwierdzenia
24,L1–L12,12,"LED adresowalny RGB, spód płytki (podświetlenie blatu)",5050 PLCC4,LED_SMD:LED_WS2812B_PLCC4_5.0x5.0mm_P3.2mm,Worldsemi,WS2812B-V5,WS2812B-V5,WS2812B 5050 SMD chip (np. BTF-LIGHTING),SMD (spód),
25,S1–S8,8,Gniazdo hotswap Kailh Choc (V1/V2),SMD,,Kailh,CPG135001S30,—,"amazon.de B0CJQHMYDW (50 szt., „Low Profile Socket … Kailh 1350”)",SMD (spód),brak w TME; lutowane od spodu na pady 1 i 2
26,S1–S8,8,"Przełącznik Kailh Choc V2 (low profile, trzpień MX)",THT (wciskany),,Kailh,CPG1353 (Choc V2),—,amazon.de B0CMZWF635 (Kailh Choc V2 Brown) lub inny Choc V2,wciskany w gniazdo,brak w TME; pasują też Choc V1 (CPG1350)
27,—,8,Keycap 1u w profilu MX (Choc V2 ma trzpień MX),—,,—,—,—,keycaps MX 1u (np. low profile),—,"raster 19,05 mm"
28,"ENC1, ENC2",2,"Gałka do enkodera, oś 6 mm D, Ø ≤ 18 mm",—,,—,—,—,potentiometer knob 6 mm D shaft,—,oś D 6 mm
29,RV1,1,Nakładka na dźwignię suwaka Bourns PTA,—,,—,—,—,slide potentiometer knob cap,—,wąska (≤ 8 mm) – patrz DESIGN_NOTES
30,J2,1,"Moduł OLED 2,42"" SSD1309 128×64 I²C, 4 piny","70,10 × 48,10 mm",,ShengYang,—,—,2.42 inch OLED SSD1309 I2C 4 pin,na gniazdo J2,jak w ChocPilot v1
31,J2,1,"Listwa kołkowa 1×4 2,54 mm do modułu (jeśli moduł jej nie ma)",THT,,Connfly,DS1021-1*4SF11,ZL201-04G,pin header 2.54 mm,THT,do potwierdzenia w TME
32,H1–H4,4,Śruba M3 × 6 + tuleja dystansowa / wkładka do obudowy,—,,—,—,—,M3 screws assortment,—,zależnie od obudowy
